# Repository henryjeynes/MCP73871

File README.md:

# MCP73871
A breakout board for the MCP73871 battery charger IC from Microchip. Includes circuitry for load sharing, temperature protection, and indicator LEDs.

If you use the resistor values in the schematic (setting the charge current to 1A), be warned that the chip will dissipate up to 3.5 watts. A larger heatsink with or without a fan is mandatory.

Feel free to use the contents of this repo in open-source, personal, or educational applications, as long as you give me credit. Don't use anything in this repo for commercial purposes without my permission. I cannot be held liable in any way for any damage caused directly or indirectly by the contents of this repo.

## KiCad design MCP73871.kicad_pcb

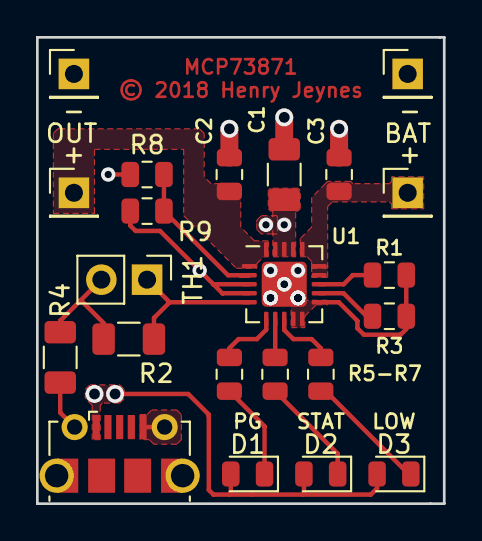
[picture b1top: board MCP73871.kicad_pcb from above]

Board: 2 copper layers, 22.6 x 25.9 mm, 22 parts (0 on the bottom side), 15 nets.

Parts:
C1: 10uF; C_1206_3216Metric
C2, C3: 4.7uF; C_0805_2012Metric
D1: PG; LED_0805_2012Metric
D2: STAT; LED_0805_2012Metric
D3: LOW; LED_0805_2012Metric
J1: MicroB; USB_Micro-B_Molex-105017-0001
J2: OUT+; PinHeader_1x01_P2.54mm_Vertical
J3: BAT+; PinHeader_1x01_P2.54mm_Vertical
J4: OUT-; PinHeader_1x01_P2.54mm_Vertical
J5: BAT-; PinHeader_1x01_P2.54mm_Vertical
R1: 1K; R_0805_2012Metric
R2: 69.8K; R_1206_3216Metric
R3: 33K; R_0805_2012Metric
R4: 1.54K; R_1206_3216Metric
R5, R6, R7: 470; R_0805_2012Metric
R8: 330K; R_0805_2012Metric
R9: 110K; R_0805_2012Metric
TH1: 10K; PinHeader_1x02_P2.54mm_Vertical
U1: MCP73871; QFN-20-1EP_4x4mm_P0.5mm_EP2.5x2.5mm

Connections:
+5V: C1.1, D1.2, D2.2, D3.2, J1.1, R8.1, U1.3, U1.4, U1.17, U1.18, U1.19
GND: C1.2, C2.2, C3.2, J1.5, J1.6, J4.1, J5.1, R1.2, R3.2, R4.2, R9.2, U1.9, U1.10, U1.11, U1.21
unnamed: C2.1, J2.1, U1.1, U1.20
unnamed: C3.1, J3.1, U1.14, U1.15, U1.16
unnamed: D1.1, R5.2
unnamed: D2.1, R6.2
unnamed: D3.1, R7.2
unnamed: R1.1, U1.13
unnamed: R2.1, TH1.1, U1.5
unnamed: R2.2, R4.1, TH1.2
unnamed: R3.1, U1.12
unnamed: R5.1, U1.6
unnamed: R6.1, U1.7
unnamed: R7.1, U1.8
unnamed: R8.2, R9.1, U1.2

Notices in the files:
MCP73871.kicad_pcb:
© 2018 Henry Jeynes
